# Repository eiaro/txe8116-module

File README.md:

# TXE8116 Module

Open-source hardware module for the TXE8116 — a 16-bit SPI I/O expander with two 8-bit ports, configurable push-pull/open-drain outputs, pull resistors, interrupt support, and per-pin glitch filtering.

## Repository Structure

```
txe8116-module/
├── hardware/          # KiCad schematic and PCB (CC BY-SA 4.0)
├── firmware/          # Driver and example code (MIT)
│   ├── esp32/         # ESP-IDF example
│   ├── zephyr/        # Zephyr RTOS examples
│   ├── raspberrypi/   # Python driver and C example
│   ├── arduino/       # Arduino example
│   └── beaglebone/    # BeagleBone C example
└── docs/              # Wiring guides
```

## Firmware

### ESP32 (ESP-IDF)

Uses the [`eiaro/txe81xx`](https://components.espressif.com/components/eiaro/txe81xx) component from the ESP component registry.

```bash
cd firmware/esp32/esp-idf/txe8116_idf
idf.py build flash monitor
```

See [`firmware/esp32/esp-idf/txe8116_idf/README.md`](firmware/esp32/esp-idf/txe8116_idf/README.md).

### Zephyr RTOS

Uses the [`xylon-labs/zephyr-txe81xx`](https://github.com/xylon-labs/zephyr-txe81xx) driver module.

| Example | Description |
|---------|-------------|
| [`firmware/zephyr/basic_gpio`](firmware/zephyr/basic_gpio/README.md) | Polling — LED mirrors button state |
| [`firmware/zephyr/gpio_interrupt`](firmware/zephyr/gpio_interrupt/README.md) | Interrupt-driven — LED toggles on button events |

```bash
west build -b nucleo_l476rg firmware/zephyr/basic_gpio
```

### Raspberry Pi (Python)

```bash
cd firmware/raspberrypi/python
python3 example.py
```

See [`firmware/raspberrypi/python/README.md`](firmware/raspberrypi/python/README.md).

## Hardware

KiCad 8.x project in [`hardware/txe8116-module/`](hardware/txe8116-module/README.md). Fabrication files (Gerbers, BOM, pick & place) are in `hardware/txe8116-module/fabrication/`.

## License

- **Hardware** (`hardware/`): [CC BY-SA 4.0](hardware/LICENSE)
- **Firmware / Software** (`firmware/`): [MIT](firmware/LICENSE)

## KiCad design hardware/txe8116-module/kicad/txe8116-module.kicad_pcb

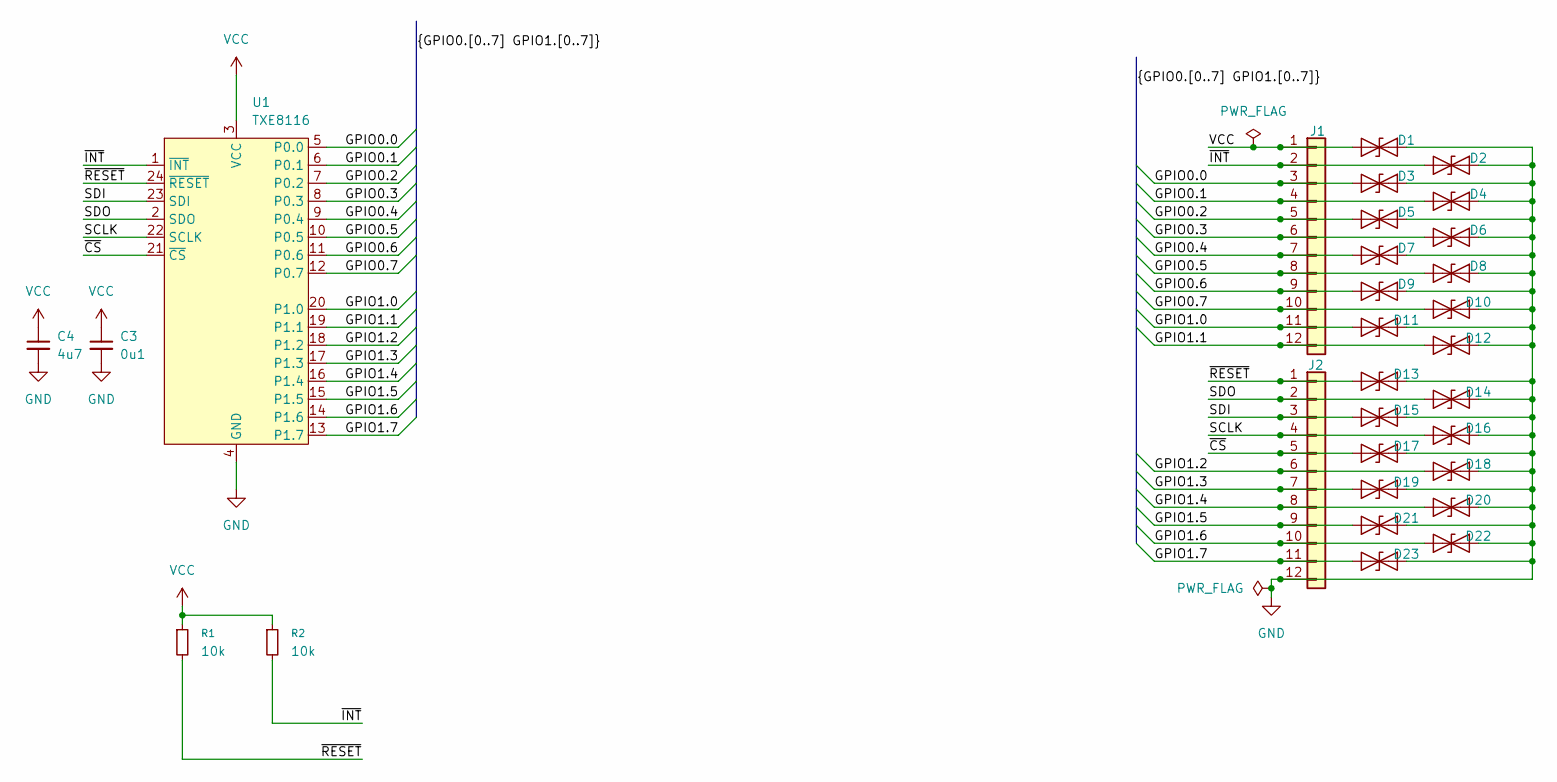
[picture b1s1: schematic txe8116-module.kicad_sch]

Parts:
C3: 0u1; C_0603_1608Metric
C4: 4u7; C_0603_1608Metric
D1, D2, D3, D4, D5, D6, D7, D8, D9, D10, D11, D12, D13, D14, D15, D16, D17, D18, D19, D20, D21, D22, D23: ESD9B5.0ST5G; D_SOD-923; MPN ESD9B5.0ST5G
J1: Conn_01x12; 1x12_P2.54mm_Castellated_Mirrored
J2: Conn_01x12; 1x12_P2.54mm_Castellated
R1, R2: 10k; R_0603_1608Metric
U1: TXE8116; Texas_DGS0024A_TSSOP-24_3x6.1mm_P0.5mm; MPN TXE8116DGSR

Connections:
/GPIO0.0: D3.1 (A1), J1.3, U1.5 (P0.0)
/GPIO0.1: D4.1 (A1), J1.4, U1.6 (P0.1)
/GPIO0.2: D5.1 (A1), J1.5, U1.7 (P0.2)
/GPIO0.3: D6.1 (A1), J1.6, U1.8 (P0.3)
/GPIO0.4: D7.1 (A1), J1.7, U1.9 (P0.4)
/GPIO0.5: D8.1 (A1), J1.8, U1.10 (P0.5)
/GPIO0.6: D9.1 (A1), J1.9, U1.11 (P0.6)
/GPIO0.7: D10.1 (A1), J1.10, U1.12 (P0.7)
/GPIO1.0: D11.1 (A1), J1.11, U1.20 (P1.0)
/GPIO1.1: D12.1 (A1), J1.12, U1.19 (P1.1)
/GPIO1.2: D18.1 (A1), J2.6, U1.18 (P1.2)
/GPIO1.3: D19.1 (A1), J2.7, U1.17 (P1.3)
/GPIO1.4: D20.1 (A1), J2.8, U1.16 (P1.4)
/GPIO1.5: D21.1 (A1), J2.9, U1.15 (P1.5)
/GPIO1.6: D22.1 (A1), J2.10, U1.14 (P1.6)
/GPIO1.7: D23.1 (A1), J2.11, U1.13 (P1.7)
/SCLK: D16.1 (A1), J2.4, U1.22 (SCLK)
/SDI: D15.1 (A1), J2.3, U1.23 (SDI)
/SDO: D14.1 (A1), J2.2, U1.2 (SDO)
/~CS: D17.1 (A1), J2.5, U1.21 (~CS)
/~INT: D2.1 (A1), J1.2, R2.2, U1.1 (~INT)
/~RESET: D13.1 (A1), J2.1, R1.2, U1.24 (~RESET)
GND: C3.2, C4.2, D1.2 (A2), D2.2 (A2), D3.2 (A2), D4.2 (A2), D5.2 (A2), D6.2 (A2), D7.2 (A2), D8.2 (A2), D9.2 (A2), D10.2 (A2), D11.2 (A2), D12.2 (A2), D13.2 (A2), D14.2 (A2), D15.2 (A2), D16.2 (A2), D17.2 (A2), D18.2 (A2), D19.2 (A2), D20.2 (A2), D21.2 (A2), D22.2 (A2), D23.2 (A2), J2.12, U1.4 (GND)
VCC: C3.1, C4.1, D1.1 (A1), J1.1, R1.1, R2.1, U1.3 (VCC)

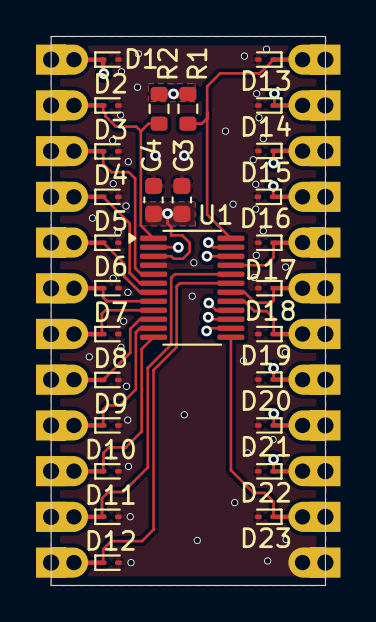
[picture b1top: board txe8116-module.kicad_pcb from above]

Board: 4 copper layers, 15.2 x 30.5 mm, 30 parts (0 on the bottom side), 24 nets.

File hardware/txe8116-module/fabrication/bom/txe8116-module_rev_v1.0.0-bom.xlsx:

|  | KiBot variants example
 |  | Schematic: | txe8116-module | Component Groups: | 5
 |  | Variant: | default | Component Count: | 28
 |  | Revision: | v1.0.0 | Fitted Components: | 28
 |  | Date: | 2026-03-24_19-54-47 | Number of PCBs: | 1
 |  | KiCad Version: | 9.0.5+1 | Total Components: | 28
Row | References | Quantity Per PCB | Value | Footprint
1 | C3 | 1 | 100 nF | C_0603_1608Metric
2 | C4 | 1 | 4.7 µF | C_0603_1608Metric
3 | D1 D2 D3 D4 D5 D6 D7 D8 D9 D10 D11 D12 D13 D14 D15 D16 D17 D18 D19 D20 D21 D22 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 | 23 | ESD9B5.0ST5G | D_SOD-923
4 | R1 R2 | 2 | 10 kΩ | R_0603_1608Metric
5 | U1 | 1 | TXE8116 | Texas_DGS0024A_TSSOP-24_3x6.1mm_P0.5mm

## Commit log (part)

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2025-10-28 Add .gitignore file for common exclusions
2025-10-28 Add licensing information to LICENSES.md
2025-10-29 Added files
2025-10-29 Update license description wording
2025-10-29 Added more structure
2025-10-29 ci: add KiCad ERC/DRC workflow and KiBot config
2025-10-29 Skeleton files
2025-10-29 CI correction
2025-10-29 Update CODEOWNERS to include hardware and firmware ownership
2025-10-29 Enhance KiBot configuration with additional output formats and improved preflight checks
2025-10-29 Fix preflight checks in KiBot configuration for ERC and DRC
2025-10-29 Add SMD resistor footprint and update schematic symbols for R_Small
2025-10-29 Add screw terminal footprint and update schematic
    - Introduced a new screw terminal footprint (WAGO 2601-1102) in the PCB layout.
    - Updated net connections for the new terminal block.
    - Modified the resistor value in the schematic to 100k.
    - Added a new connector symbol for the screw terminal in the schematic.
    - Enhanced the schematic with additional wire connections for better clarity.
2025-10-30 Add Dockerfile for KiBot with KiCad 9.0.5
2025-10-30 Add README for KiBot Docker Image
    This README provides information about the KiBot Docker image for txe8116-module, including usage instructions for local development and CI/CD.
2025-10-30 Add GitHub Actions workflow for Docker build
2025-10-30 Refactor Dockerfile to handle existing user UID
    Updated Dockerfile to create a non-root user if UID 1000 exists and ensure proper ownership of the workspace directory.
2025-10-30 Modify container image and credentials in CI workflow
    Updated container configuration for the Hardware CI workflow.
2025-10-30 Simplify Dockerfile by removing non-root user setup
    Removed non-root user creation for CI/CD containers and adjusted user context.
2025-10-30 Add options to use root user in CI workflow
2025-10-30 Modify KiBot installation command in Dockerfile
    Updated pip install command for KiBot to include --no-compile option.
2025-10-30 Update Dockerfile to use KiCad 9.0.5 image
2025-10-30 Update Dockerfile to install KiCad 9.x
    Added KiCad official Debian repository for version 9.x and updated installation commands.
2025-10-30 Enhance Dockerfile for KiCad installation
    Updated the Dockerfile to install additional KiCad packages and clean up unnecessary files.
2025-10-30 Added some components
2025-10-30 Add text variables for date and git hash in project configuration
    - Updated the text_variables section in the txe8116-module.kicad_pro file to include the current date and the git hash for better version tracking.
2025-10-30 Fix KiBot command arguments for ERC/DRC checks and update .gitignore for additional KiCad files
2025-10-30 Change 3D model type and clean up config
    Updated 3D model type and removed unnecessary top view render.
2025-10-30 Remove 3D top view HQ render configuration
    Removed 3D top view high-quality render configuration from .kibot.yaml.
2025-11-02 Refactor code structure for improved readability and maintainability
2025-11-02 Update .gitignore and modify 3D model reference in Texas_DGS0024A footprint
2025-11-02 Add PWR_FLAG symbols to indicate power source for ERC checks
2025-11-02 Asiler custom bridges causes DRC - Moved to a seperate layer - Move to Edge.Cut if manufactured at Aisler
2025-11-02 Remove variant title from PDF schematic and print options
2025-11-02 Adjust component properties and positions for improved layout and visibility
2025-11-02 Remove options section from Schematic PDF output configuration
2025-11-02 Refactor netclass assignments and update component properties for improved clarity
2025-12-07 Add TXE8116 Python driver and example for Raspberry Pi integration
2025-12-07 Add TXE81xx driver header and implementation files for ESP32
2025-12-07 Add README for TXE8116 ESP-IDF driver with basic description
2025-12-10 Add SCEA154 and TXE8116 datasheet PDFs
    Added datasheet documents for SCEA154 and TXE8116 components to the docs/datasheet directory for reference.
2026-03-23 docs: add README for ESP32 IDF and Zephyr examples
2026-03-23 docs: add root README
2026-03-24 fix(hardware): add 10k pull-up resistors on RESET and INT per datasheet
2026-03-24 chore: untrack fp-info-cache (already in .gitignore)
2026-03-24 chore(hardware): set revision to v1.0.0
2026-03-24 ci: auto-commit generated docs and fabrication files after main build
2026-03-24 ci: use peter-evans/create-pull-request for generated files
2026-03-24 ci: add workflow_dispatch trigger
2026-03-24 fix(ci): run artifact PR step on workflow_dispatch too
2026-03-24 chore: update generated docs and fabrication files
2026-03-24 chore: exclude checks/ from version control
    KiBot uses checks/ as a temporary output directory during CI. The
    relevant files are copied to docs/ and fabrication/ by the workflow,
    so the checks/ directory itself should not be tracked.
2026-03-24 chore: exclude checks/ from version control (#25)
    KiBot uses checks/ as a temporary output directory during CI. The
    relevant files are copied to docs/ and fabrication/ by the workflow,
    so the checks/ directory itself should not be tracked.
2026-03-24 chore: update generated docs and fabrication files (#24)
